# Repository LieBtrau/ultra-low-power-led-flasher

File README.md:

# Ultra low power LED

The original project has been designed in [2020](./2020/).  See more about this project on [Hackaday.io](https://hackaday.io/project/169882-ultra-low-power-led).

In [2026](./2026/DN_ulp-flasher.md), the idea has been reused to create a "glow-in-the-dark" like effect for a night light.  The RTC has been replaced by a [low power oscillator](http://www.discovercircuits.com/H-Corner/Ultra%20low%20current%20oscillator.htm), also used by Stephan's [Yet another ultra low power LED](https://hackaday.io/project/203844-yet-another-ultra-low-power-led).

* [Development report ](./2026/DN_ulp-flasher.md)
* [Test report](./2026/TR_ulp-flasher.md)
* [After Action report](./2026/Info/AAR.md)

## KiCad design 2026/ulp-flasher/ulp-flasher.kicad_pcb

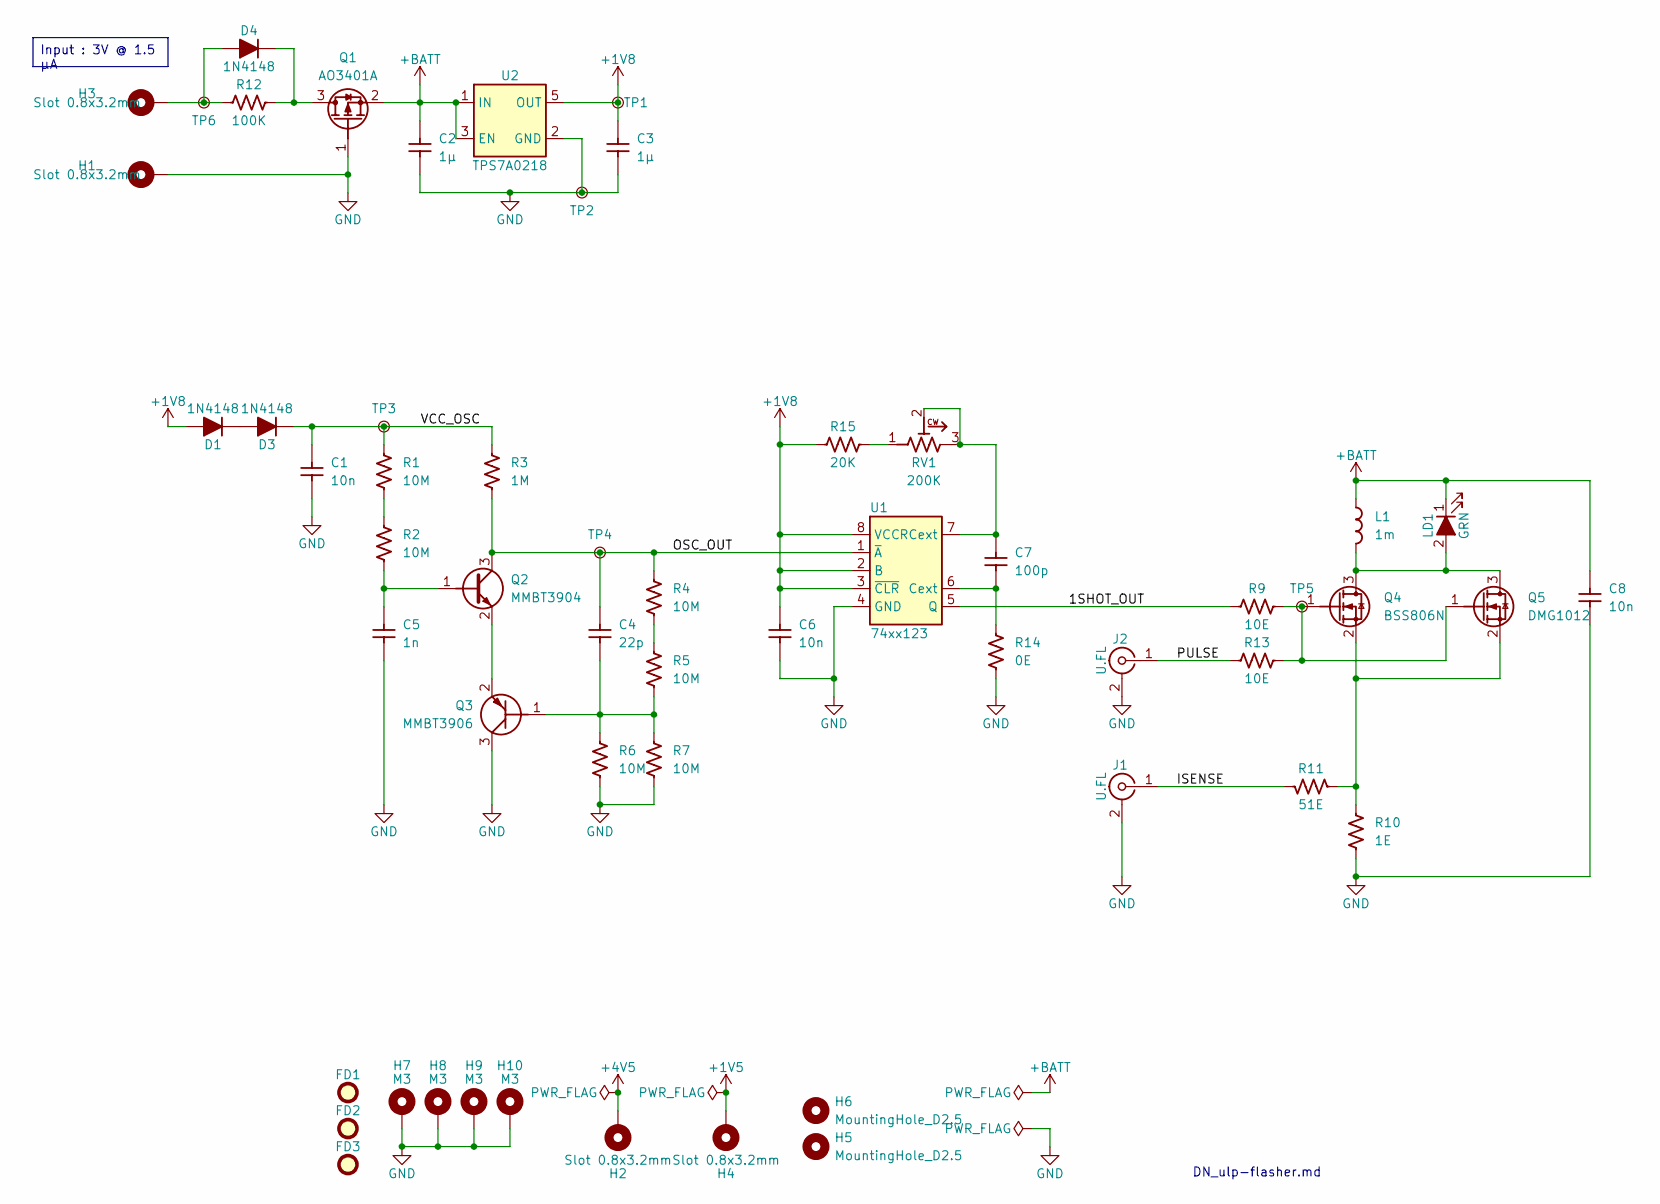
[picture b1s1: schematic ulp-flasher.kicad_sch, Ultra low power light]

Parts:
C1, C6, C8: 10n; C_0603_1608Metric; Voltage 50; Tolerance ±10%; MPN GCM188R71H103KA37D; LCSC C57112
C2, C3: 1µ; C_0603_1608Metric; Voltage 50; Tolerance ±10%; MPN CL10A105KB8NNNC; LCSC C15849
C4: 22p; C_0603_1608Metric; Voltage 50; Tolerance ±5%; MPN CL10C220JB8NNNC; LCSC C1653
C5: 1n; C_0603_1608Metric; Voltage 50; Tolerance ±10%; MPN CL10B102KB8NNNC; LCSC C1588
C7: 100p; C_0603_1608Metric; Voltage 50; Tolerance ±5%; MPN CL10C101JB8NNNC; LCSC C14858
D1, D3, D4: 1N4148; D_SOD-323; Voltage 100V; MPN 1N4148WS; LCSC C2128
FD1, FD2, FD3: Fiducial; Fiducial_1mm_Mask2mm
H1, H2, H3, H4: Slot 0.8x3.2mm; MountingHole_0.8x3.2mm
H5, H6: MountingHole_D2.5; MountingHole_2.5mm
H7, H8, H9, H10: M3; MountingHole_3.2mm_M3_Pad_Via
J1, J2: U.FL; U.FL_Hirose_U.FL-R-SMT-1_Vertical; MPN U.FL-R-SMT-1(10); LCSC C5137195
L1: 1m; L_Wurth_WE-LQS-6045; MPN 74404064102; LCSC C5339743
LD1: GRN; LED_PLCC_2835; MPN GT JTLPS1.13-KKLN-25-1-150-R33; LCSC C17637249
Q1: AO3401A; SOT-23-3; MPN AO3401A; LCSC C15127
Q2: MMBT3904; SOT-23-3; MPN MMBT3904-7-F; LCSC C20526
Q3: MMBT3906; SOT-23-3; MPN MMBT3906LT1G; LCSC C53444
Q4: BSS806N; SOT-23-3; MPN BSS806NH6327-HXY; LCSC C20606241
Q5: DMG1012; SOT-523; MPN DMG1012T-7; LCSC C7473321
R1, R2, R4, R5, R6, R7: 10M; R_0603_1608Metric; Tolerance 1%; MPN 0603WAF1005T5E; LCSC C7250
R3: 1M; R_0603_1608Metric; Tolerance 1%; MPN RC0603FR-071ML; LCSC C22935
R9, R13: 10E; R_0603_1608Metric; Tolerance 1%; MPN 0603WAF100JT5E; LCSC C22859
R10: 1E; R_0603_1608Metric; Tolerance 1%; MPN 0603WAF100KT5E; LCSC C22936
R11: 51E; R_0603_1608Metric; Tolerance 1%; MPN 0603WAF510JT5E; LCSC C23197
R12: 100K; R_0603_1608Metric; Tolerance 1%; MPN RC0603FR-07100KL; LCSC C25803
R14: 0E; R_0603_1608Metric; Tolerance 0; MPN RC0603FR-070RL; LCSC C21189
R15: 20K; R_0603_1608Metric; Tolerance 1%; MPN RC0603FR-0720KL; LCSC C4184
RV1: 200K; Potentiometer_Bourns_3314J_Vertical; Tolerance 20.00%; MPN 3314J-1-204E; LCSC C124643
TP1, TP2, TP3, TP4, TP5, TP6: TestPoint; TestPoint_Pad_D1.0mm
U1: 74xx123; TSSOP-8_3x3mm_P0.65mm; MPN 74LVC1G123DP,125; LCSC C513291
U2: TPS7A0218; SOT-23-5; MPN TPS7A0218PDBVR; LCSC C3748843

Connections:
+1V5: H4.1 (1_1)
+1V8: C3.2, C6.2, D1.2 (A), R15.2, TP1.1 (1_1), U1.2 (B), U1.3 (~CLR), U1.8 (VCC), U2.5 (OUT)
+4V5: H2.1 (1_1)
+BATT: C2.2, C8.2, L1.1, LD1.1 (C), Q1.2 (S), U2.1 (IN), U2.3 (EN)
/1SHOT_OUT: R9.1, U1.5 (Q)
/ISENSE: J1.1 (In), R11.2
/OSC_OUT: C4.2, Q2.3 (C), R3.1, R4.2, TP4.1 (1_1), U1.1 (~A)
/PULSE: J2.1 (In), R13.1
/VCC_OSC: C1.2, D3.1 (K), R1.2, R3.2, TP3.1 (1_1)
GND: C1.1, C2.1, C3.1, C5.1, C6.1, C8.1, H1.1 (1_1), H7.1 (1_1), H8.1 (1_1), H9.1 (1_1), H10.1 (1_1), J1.2 (Ext), J2.2 (Ext), Q1.1 (G), Q3.3 (C), R6.1, R7.1, R10.1, R14.1, TP2.1 (1_1), U1.4 (GND), U2.2 (GND)
unnamed: D1.1 (K), D3.2 (A)
unnamed: D4.2 (A), H3.1 (1_1), R12.1, TP6.1 (1_1)
unnamed: D4.1 (K), Q1.3 (D), R12.2
unnamed: L1.2, LD1.2 (A), Q4.3 (D), Q5.3 (D)
unnamed: C5.2, Q2.1 (B), R2.1
unnamed: Q2.2 (E), Q3.2 (E)
unnamed: C4.1, Q3.1 (B), R5.1, R6.2, R7.2
unnamed: Q4.1 (G), Q5.1 (G), R9.2, R13.2, TP5.1 (1_1)
unnamed: Q4.2 (S), Q5.2 (S), R10.2, R11.1
unnamed: R1.1, R2.2
unnamed: R4.1, R5.2
unnamed: R15.1, RV1.1
unnamed: C7.1, R14.2, U1.6 (Cext)
unnamed: C7.2, RV1.2, RV1.3, U1.7 (RCext)

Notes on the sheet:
DN_ulp-flasher.md
Input : 3V @ 1.5 µA

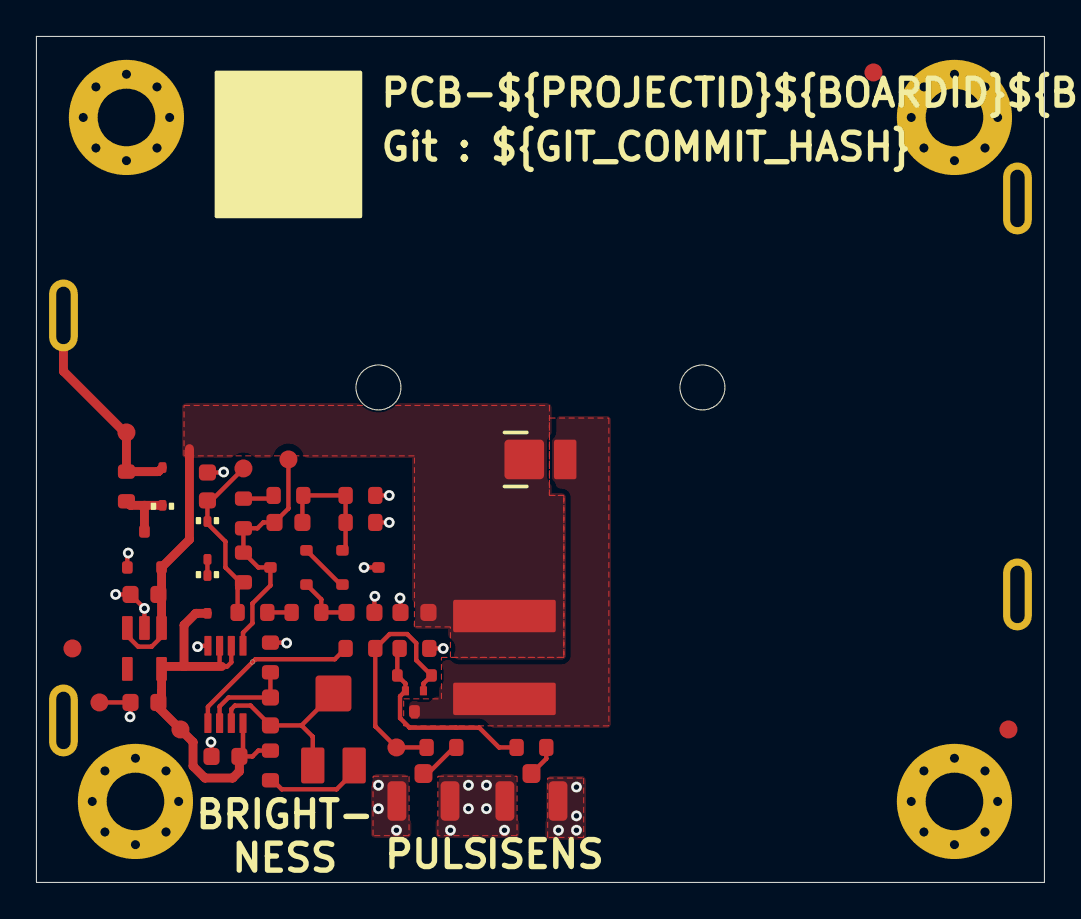
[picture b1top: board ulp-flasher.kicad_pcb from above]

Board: 2 copper layers, 56.0 x 47.0 mm, 56 parts (0 on the bottom side), 22 nets.

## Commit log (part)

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2020-04-18 Working version of the bitbang library
2020-04-24 First writes to RV-3028-C7 are OK
2020-04-25 RTC generates 64Hz clock output
2020-06-18 Migrating to Adafruit ProTrinket 3V
2020-10-03 Correcting README.md
2021-08-15 Adding license statement + pin connections
